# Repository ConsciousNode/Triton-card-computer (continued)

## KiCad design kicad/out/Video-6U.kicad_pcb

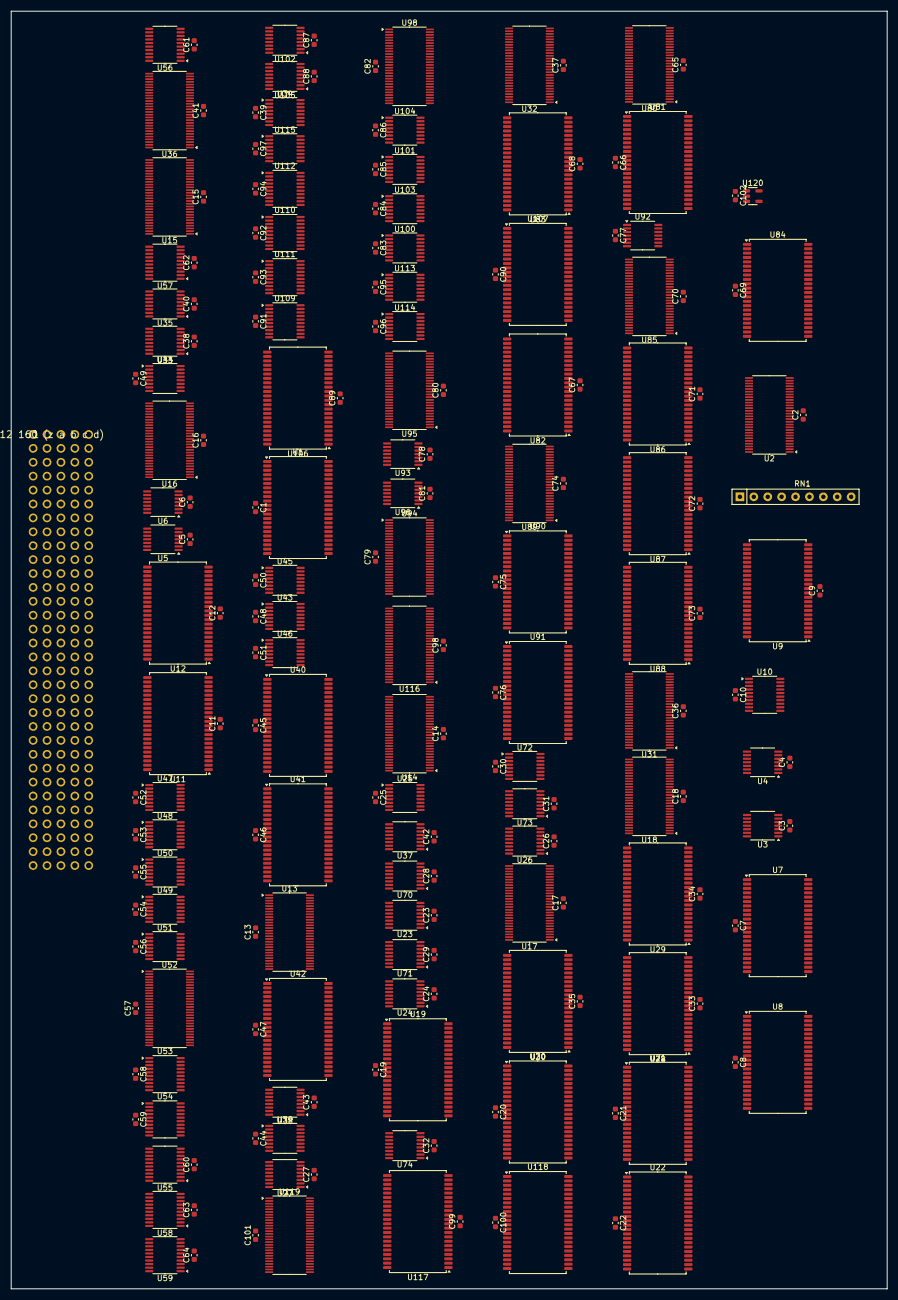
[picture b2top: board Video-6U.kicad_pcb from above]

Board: 4 copper layers, 160.0 x 233.3 mm, 206 parts (0 on the bottom side), 589 nets, no tracks yet.

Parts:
C1, C2, C3, C4, C5, C6, C7, C8, C9, C10, C11, C12, C13, C14, C15, C16, C17, C18, C19, C20, C21, C22, C23, C24, C25, C26, C27, C28, C29, C30, C31, C32, C33, C34, C35, C36, C37, C38, C39, C40, C41, C42, C43, C44, C45, C46, C47, C48, C49, C50, C51, C52, C53, C54, C55, C56, C57, C58, C59, C60, C61, C62, C63, C64, C65, C66, C67, C68, C69, C70, C71, C72, C73, C74, C75, C76, C77, C78, C79, C80, C81, C82, C83, C84, C85, C86, C87, C88, C89, C90, C91, C92, C93, C94, C95, C96, C97, C98, C99, C100, C101, C102: 100n; C_0603_1608Metric
J1: DIN41612 160 (z a b c d)
RN1: RPACK8; R_Array_SIP9
U1, U7, U8, U9, U19, U20, U21, U22, U40, U41, U42, U81, U82, U83, U84, U86, U87, U88, U90, U91, U117, U118: IS61WV5128; TSOP-II-44_10.16x18.41mm_P0.8mm
U2, U13, U14, U15, U16, U17, U18, U31, U32, U36, U52, U80, U85, U89, U94, U95, U98, U116, U119: ALVCH16823; TSSOP-56_6.1x14mm_P0.5mm
U3, U93: LVC04; TSSOP-14_4.4x5mm_P0.65mm
U4: LVC32; TSSOP-14_4.4x5mm_P0.65mm
U5, U6, U92, U96: LVC08; TSSOP-14_4.4x5mm_P0.65mm
U10: LVC574; TSSOP-20_4.4x6.5mm_P0.65mm
U11, U12, U28, U29, U30: IS61WV20488; TSOP-II-44_10.16x18.41mm_P0.8mm
U23, U24, U25, U26, U27, U33, U34, U35, U37, U38, U39, U70, U71, U72, U73, U74, U100, U101, U102, U103, U104, U105, U113, U114, U115: LVC157; TSSOP-16_4.4x5mm_P0.65mm
U43, U44, U45, U46, U47, U48, U49, U50, U51: LVC153; TSSOP-16_4.4x5mm_P0.65mm
U53, U54, U55, U56, U57, U58, U59, U109, U110, U111, U112: LVC245; TSSOP-20_4.4x6.5mm_P0.65mm
U106, U107: IS61WV51216; TSOP-II-44_10.16x18.41mm_P0.8mm
U120: LVC1G07; SOT-23-5

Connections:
+3V3: C1.1, C2.1, C3.1, C4.1, C5.1, C6.1, C7.1, C8.1, C9.1, C10.1, C11.1, C12.1, C13.1, C14.1, C15.1, C16.1, C17.1, C18.1, C19.1, C20.1, C21.1, C22.1, C23.1, C24.1, C25.1, C26.1, C27.1, C28.1, C29.1, C30.1, C31.1, C32.1, C33.1, C34.1, C35.1, C36.1, C37.1, C38.1, C39.1, C40.1, C41.1, C42.1, C43.1, C44.1, C45.1, C46.1, C47.1, C48.1, C49.1, C50.1, C51.1, C52.1, C53.1, C54.1, C55.1, C56.1, C57.1, C58.1, C59.1, C60.1, C61.1, C62.1, C63.1, C64.1, C65.1, C66.1, C67.1, C68.1, C69.1, C70.1, C71.1, C72.1, C73.1, C74.1, C75.1, C76.1, C77.1, C78.1, C79.1, C80.1, C81.1, C82.1, C83.1, C84.1, C85.1, C86.1, C87.1, C88.1, C89.1, C90.1, C91.1, C92.1, C93.1, C94.1, C95.1, C96.1, C97.1, C98.1, C99.1, C100.1, C101.1, C102.1, J1.z2, J1.z4, J1.z6, J1.z10, J1.z12, J1.z14, J1.z18, J1.z20, J1.z22, J1.z26, J1.z28, J1.z30, RN1.1, U1.11, U1.15, U1.33, U2.1, U2.7, U2.22, U2.28, U2.35, U2.50, U3.14, U4.14, U5.14, U6.14, U7.11, U7.15, U7.33, U8.11, U8.15, U8.33, U9.11, U9.15, U9.33, U10.20, U11.11, U11.15, U11.33, U12.11, U12.15, U12.33, U13.1, U13.7, U13.22, U13.28, U13.35, U13.50, U14.1, U14.7, U14.22, U14.28, U14.35, U14.50, U15.1, U15.7, U15.22, U15.28, U15.35, U15.50, U16.1, U16.7, U16.22, U16.28, U16.35, U16.50, U17.1, U17.7, U17.22, U17.28, U17.35, U17.50, U18.1, U18.7, U18.22, U18.28, U18.35, U18.50, U19.11, U19.15, U19.33, U20.11, U20.15, U20.33, U21.11, U21.15, U21.33, U22.11, U22.15, U22.33, U23.16, U24.16, U25.16, U26.16, U27.16, U28.11, U28.15, U28.33, U29.11, U29.15, U29.33, U30.11, U30.15, U30.33, U31.1, U31.7, U31.22, U31.28, U31.35, U31.50, U32.1, U32.7, U32.22, U32.28, U32.35, U32.50, U33.16, U34.16, U35.16, U36.1, U36.7, U36.22, U36.28, U36.35, U36.50, U37.16, U38.16, U39.16, U40.11, U40.15, U40.33, U41.11, U41.15, U41.33, U42.11, U42.15, U42.33, U43.16, U44.16, U45.16, U46.16, U47.16, U48.16, U49.16, U50.16, U51.16, U52.1, U52.7, U52.22, U52.28, U52.35, U52.50, U53.1, U53.20, U54.1, U54.20, U55.1, U55.20, U56.1, U56.20, U57.1, U57.20, U58.1, U58.20, U59.1, U59.20, U70.16, U71.16, U72.16, U73.16, U74.16, U80.1, U80.7, U80.22, U80.28, U80.35, U80.50, U81.11, U81.15, U81.33, U82.11, U82.15, U82.33, U83.11, U83.15, U83.33, U84.11, U84.15, U84.33, U85.1, U85.7, U85.22, U85.28, U85.35, U85.50, U86.11, U86.15, U86.33, U87.11, U87.15, U87.33, U88.11, U88.15, U88.33, U89.1, U89.7, U89.22, U89.28, U89.35, U89.50, U90.11, U90.15, U90.33, U91.11, U91.15, U91.33, U92.14, U93.14, U94.1, U94.7, U94.22, U94.28, U94.35, U94.50, U95.1, U95.7, U95.22, U95.28, U95.35, U95.50, U96.14, U98.1, U98.7, U98.22, U98.28, U98.35, U98.50, U100.16, U101.16, U102.16, U103.16, U104.16, U105.16, U106.11, U106.33, U107.11, U107.33, U109.1, U109.20, U110.1, U110.20, U111.1, U111.20, U112.1, U112.20, U113.16, U114.16, U115.16, U116.1, U116.7, U116.22, U116.28, U116.35, U116.50, U117.11, U117.15, U117.33, U118.11, U118.15, U118.33, U119.1, U119.7, U119.22, U119.28, U119.35, U119.50, U120.5
+5V: J1.z8, J1.z16, J1.z24, J1.z32
/ADB: U93.10, U107.41
/BOE: U4.3, U53.19, U54.19, U55.19, U56.19, U57.19, U58.19, U59.19
/CEDGE: J1.c13, U7.19, U8.19
/F2B: U93.4, U96.2
/FACTV: U92.13, U93.2
/FCE: U3.8, U17.30, U17.55, U18.30, U18.55
/IOCE: U5.3, U52.30, U52.55
/LDC: U7.14, U16.30, U16.55
/LDIO: U5.1, U7.36
/LDP: U7.13, U15.30, U15.55
/LDX: U7.9, U13.30, U13.55
/LDY: U7.10, U14.55
/R2: U3.4, U5.2
/SWRD: U9.14, U10.5
/SWRQ: U4.4, U10.16
/VSEL: U3.6, U4.2
/VSLD: U8.14, U14.30
/WEA: U93.6, U106.17, U109.19, U110.19
/WEB: U93.8, U107.17, U111.19, U112.19
ADB: U93.11, U98.16, U100.1, U101.1, U102.1, U103.1, U104.1, U105.1, U106.41, U113.1, U114.1, U115.1
AHS: U98.19, U116.37
APIC: U98.17, U116.38
AVS: U98.20, U116.36
AX0: U98.3, U100.2, U103.3
AX1: U98.5, U100.5, U103.6
AX2: U98.6, U100.11, U103.10
AX3: U98.8, U100.14, U103.13
AX4: U98.9, U101.2, U104.3
AX5: U98.10, U101.5, U104.6
AX6: U98.12, U101.11, U104.10
AX7: U98.13, U101.14, U104.13
AX8: U98.14, U102.2, U105.3
AX9: U98.15, U102.5, U105.6
BHS: U116.20, U119.38
BP0: U116.3, U117.3, U118.3
BP1: U116.5, U117.4, U118.4
BP2: U116.6, U117.5, U118.5
BP3: U116.8, U117.6, U118.6
BP4: U116.9, U117.7, U118.7
BP5: U116.10, U117.16, U118.16
BP6: U116.12, U117.17, U118.17
BP7: U116.13, U117.18, U118.18
BP8: U116.14, U117.19, U118.19
BP9: U116.15, U117.20, U118.20
BP10: U116.16, U117.26, U118.26
BP11: U116.17, U117.27, U118.27
BPIC: U116.19, U117.29, U118.29
BVS: U116.21, U119.37
CI0: U11.9, U13.54, U14.54
CI1: U11.10, U13.52, U14.52
CI2: U11.13, U13.51, U14.51
CI3: U11.14, U13.49, U14.49
CI4: U11.31, U13.48, U14.48
CI5: U11.32, U13.47, U14.47
CI6: U11.35, U13.45, U14.45
CI7: U11.36, U13.44, U14.44
CI8: U12.9, U13.43, U14.43
CI9: U12.10, U13.42
CLK: J1.c10, U2.29, U2.56
CNTADV: U4.9, U9.32
CNTRST: U4.10, U9.35, U19.27, U20.27, U21.27, U22.27
CO0: U23.4, U70.2
CO1: U23.7, U70.5
CO2: U23.9, U70.11
CO3: U23.12, U70.14
CO4: U24.4, U71.2
CO5: U24.7, U71.5
CO6: U24.9, U71.11
CO7: U24.12, U71.14
CO8: U25.4, U72.2
CO9: U25.7, U72.5
CO10: U25.9, U72.11
CO11: U25.12, U72.14
CO12: U26.4, U73.2
CO13: U26.7, U73.5
CO14: U26.9, U73.11
CO15: U26.12, U73.14
CO16: U27.4, U74.2
CO17: U27.7, U74.5
CO18: U27.9, U74.11
CQ0: U28.3, U29.3, U30.3, U70.4
CQ1: U28.4, U29.4, U30.4, U70.7
CQ2: U28.5, U29.5, U30.5, U70.9
CQ3: U28.6, U29.6, U30.6, U70.12
CQ4: U28.7, U29.7, U30.7, U71.4
CQ5: U28.16, U29.16, U30.16, U71.7
CQ6: U28.17, U29.17, U30.17, U71.9
CQ7: U28.18, U29.18, U30.18, U71.12
CQ8: U28.19, U29.19, U30.19, U72.4
CQ9: U28.20, U29.20, U30.20, U72.7
CQ10: U28.26, U29.26, U30.26, U72.9
CQ11: U28.27, U29.27, U30.27, U72.12
CQ12: U28.28, U29.28, U30.28, U73.4
CQ13: U28.29, U29.29, U30.29, U73.7
CQ14: U28.30, U29.30, U30.30, U73.9
CQ15: U28.38, U29.38, U30.38, U73.12
CQ16: U28.39, U29.39, U30.39, U74.4
CQ17: U28.40, U29.40, U30.40, U74.7
CQ18: U28.41, U29.41, U30.41, U74.9
CSD0: U1.9, U2.54
CSD1: U1.10, U2.52
CSD2: U1.13, U2.51
CT0: U40.9, U43.6
CT1: U40.10, U43.10
CT2: U40.13, U44.6
CT3: U40.14, U44.10
CT4: U40.31, U45.6
CT5: U40.32, U45.10
CT6: U40.35, U46.6
CT7: U40.36, U46.10
CT8: U41.9, U47.6
CT9: U41.10, U47.10
CT10: U41.13, U48.6
CT11: U41.14, U48.10
CT12: U41.31, U49.6
CT13: U41.32, U49.10
CT14: U41.35, U50.6
CT15: U41.36, U50.10
CT16: U42.9, U51.6
CT17: U42.10, U51.10
CW_/BIO: RN1.4, U2.6, U4.1
CW_/IN: RN1.2, U2.3, U7.17, U8.18
CW_/OUT: RN1.3, U2.5, U7.18
CX0: U37.4, U40.3, U41.3, U42.3
CX1: U37.7, U40.4, U41.4, U42.4
CX2: U37.9, U40.5, U41.5, U42.5
CX3: U37.12, U40.6, U41.6, U42.6
CX4: U38.4, U40.7, U41.7, U42.7
CX5: U38.7, U40.16, U41.16, U42.16
CX6: U38.9, U40.17, U41.17, U42.17
CX7: U38.12, U40.18, U41.18, U42.18
CX8: U39.4, U40.19, U41.19, U42.19
CX9: U39.7, U40.20, U41.20, U42.20
D0+: J1.a1, U11.3, U12.3, U15.54, U16.54, U53.18
D0-: J1.a2, U11.4, U12.4, U15.52, U16.52, U53.17
D1+: J1.a3, U11.5, U12.5, U15.51, U16.51, U53.16
D1-: J1.a4, U11.6, U12.6, U15.49, U16.49, U53.15
D2+: J1.a5, U11.7, U12.7, U15.48, U16.48, U53.14
D2-: J1.a6, U11.16, U12.16, U15.47, U16.47, U53.13
D3+: J1.a7, U5.4, U11.17, U12.17, U53.12
D3-: J1.a9, U5.9, U11.18, U12.18, U53.11
D4+: J1.a10, U5.12, U11.19, U12.19, U54.18
D4-: J1.a11, U6.1, U11.20, U12.20, U54.17
D5+: J1.a12, U6.4, U11.26, U12.26, U54.16
D5-: J1.a13, U6.9, U11.27, U12.27, U54.15
D6+: J1.a14, U11.28, U12.28, U54.14
D6-: J1.a15, U11.29, U12.29, U54.13
D7+: J1.a17, U11.30, U12.30, U54.12
D7-: J1.a18, U11.38, U12.38, U54.11
D8+: J1.a19, U11.39, U12.39, U55.18
D8-: J1.a20, U11.40, U12.40, U55.17
D9+: J1.a21, U55.16
D9-: J1.a22, U55.15
D10+: J1.a23, U55.14
D10-: J1.a25, U55.13
D11+: J1.a26, U55.12
D11-: J1.a27, U55.11
D12+: J1.a28, U56.18
D12-: J1.a29, U56.17
D13+: J1.a30, U56.16
D13-: J1.a31, U56.15
D14+: J1.b1, U56.14
D14-: J1.b2, U56.13
D15+: J1.b3, U56.12
D15-: J1.b4, U56.11
D16+: J1.b5, U57.18
D16-: J1.b6, U57.17
D17+: J1.b7, U57.16
D17-: J1.b9, U57.15
D18+: J1.b10, U57.14
D18-: J1.b11, U57.13
D19+: J1.b12, U57.12
D19-: J1.b13, U57.11
D20+: J1.b14, U58.18
D20-: J1.b15, U58.17
D21+: J1.b17, U58.16
D21-: J1.b18, U58.15
D22+: J1.b19, U58.14
D22-: J1.b20, U58.13
D23+: J1.b21, U58.12
D23-: J1.b22, U58.11
D24+: J1.b23, U59.18
D24-: J1.b25, U59.17
D25+: J1.b26, U59.16
D25-: J1.b27, U59.15
D26+: J1.b28, U59.14
D26-: J1.b29, U59.13
DB: U87.32, U98.41
F1B: U94.16, U95.41
F1V: U94.17, U95.40
F1X0: U94.3, U95.54
F1X1: U94.5, U95.52
F1X2: U94.6, U95.51
F1X3: U94.8, U95.49
F1X4: U94.9, U95.48
F1X5: U94.10, U95.47
F1X6: U94.12, U95.45
F1X7: U94.13, U95.44
F1X8: U94.14, U95.43
F1X9: U94.15, U95.42
F2B: U93.3, U95.16, U96.5
F2V: U95.17, U96.1, U96.4
F2X0: U95.3, U100.3, U103.2
F2X1: U95.5, U100.6, U103.5
F2X2: U95.6, U100.10, U103.11
F2X3: U95.8, U100.13, U103.14
F2X4: U95.9, U101.3, U104.2
F2X5: U95.10, U101.6, U104.5
F2X6: U95.12, U101.10, U104.11
F2X7: U95.13, U101.13, U104.14
F2X8: U95.14, U102.3, U105.2
F2X9: U95.15, U102.6, U105.5
FACT: U89.16, U92.1
FACT2: U92.3, U92.4
FACTV: U92.6, U92.9, U93.1
FB: U87.35, U94.41
FC0: U16.3, U33.3, U43.5
FC1: U16.5, U33.6, U43.11
FC2: U16.6, U33.10, U44.5
FC3: U16.8, U33.13, U44.11
FC4: U16.9, U34.3, U45.5
FC5: U16.10, U34.6, U45.11
FC6: U16.12, U34.10, U46.5
FC7: U16.13, U34.13, U46.11
FC8: U16.14, U35.3, U47.5
FC9: U16.15, U35.6, U47.11
FC10: U16.16, U35.10, U48.5
FC11: U16.17, U35.13, U48.11
FCNT: U3.9, U4.8
FDONE: U9.17, U22.10
FFXN0: U89.54, U90.9
FFXN1: U89.52, U90.10
FFXN2: U89.51, U90.13
FFXN3: U89.49, U90.14
FFXN4: U89.48, U90.31
FFXN5: U89.47, U90.32
FFXN6: U89.45, U90.35
FFXN7: U89.44, U90.36
FFXN8: U89.43, U91.9
FFXN9: U89.42, U91.10
FL: U9.16, U10.17, U23.1, U24.1, U25.1, U26.1, U27.1, U33.1, U34.1, U35.1
FLINE: U87.31, U92.2
FNOW: U28.42, U29.42, U30.42, U70.1, U71.1, U72.1, U73.1, U74.1, U90.27, U91.27, U92.8, U94.40
FREE: U3.2, U92.10, U92.12
FREEOP: U9.18, U92.11
FWIN: U84.9, U92.5
FX0: U17.3, U19.3, U20.3, U23.3
FX1: U17.5, U19.4, U20.4, U23.6
FX2: U17.6, U19.5, U20.5, U23.10
FX3: U17.8, U19.6, U20.6, U23.13
FX4: U17.9, U19.7, U20.7, U24.3
FX5: U17.10, U19.16, U20.16, U24.6
FX6: U17.12, U19.17, U20.17, U24.10
FX7: U17.13, U19.18, U20.18, U24.13
FX8: U17.14, U19.19, U20.19, U25.3
FX9: U17.15, U19.20, U20.20, U25.6
FXC0: U70.3, U89.3, U90.3, U91.3, U94.54
FXC1: U70.6, U89.5, U90.4, U91.4, U94.52
FXC2: U70.10, U89.6, U90.5, U91.5, U94.51
FXC3: U70.13, U89.8, U90.6, U91.6, U94.49
FXC4: U71.3, U89.9, U90.7, U91.7, U94.48
FXC5: U71.6, U89.10, U90.16, U91.16, U94.47
FXC6: U71.10, U89.12, U90.17, U91.17, U94.45
FXC7: U71.13, U89.13, U90.18, U91.18, U94.44
FXC8: U72.3, U89.14, U90.19, U91.19, U94.43
FXC9: U72.6, U89.15, U90.20, U91.20, U94.42
FXN0: U17.54, U19.9
FXN1: U17.52, U19.10
FXN2: U17.51, U19.13
FXN3: U17.49, U19.14
FXN4: U17.48, U19.31
FXN5: U17.47, U19.32
FXN6: U17.45, U19.35
FXN7: U17.44, U19.36
FXN8: U17.43, U20.9
FXN9: U17.42, U20.10
FY0: U18.3, U21.3, U22.3, U25.10
FY1: U18.5, U21.4, U22.4, U25.13
FY2: U18.6, U21.5, U22.5, U26.3
FY3: U18.8, U21.6, U22.6, U26.6
FY4: U18.9, U21.7, U22.7, U26.10
FY5: U18.10, U21.16, U22.16, U26.13
FY6: U18.12, U21.17, U22.17, U27.3
FY7: U18.13, U21.18, U22.18, U27.6
FY8: U18.14, U21.19, U22.19, U27.10
FYN0: U18.54, U21.9
FYN1: U18.52, U21.10
FYN2: U18.51, U21.13
FYN3: U18.49, U21.14
FYN4: U18.48, U21.31
FYN5: U18.47, U21.32
FYN6: U18.45, U21.35
FYN7: U18.44, U21.36
FYN8: U18.43, U22.9
GND: C1.2, C2.2, C3.2, C4.2, C5.2, C6.2, C7.2, C8.2, C9.2, C10.2, C11.2, C12.2, C13.2, C14.2, C15.2, C16.2, C17.2, C18.2, C19.2, C20.2, C21.2, C22.2, C23.2, C24.2, C25.2, C26.2, C27.2, C28.2, C29.2, C30.2, C31.2, C32.2, C33.2, C34.2, C35.2, C36.2, C37.2, C38.2, C39.2, C40.2, C41.2, C42.2, C43.2, C44.2, C45.2, C46.2, C47.2, C48.2, C49.2, C50.2, C51.2, C52.2, C53.2, C54.2, C55.2, C56.2, C57.2, C58.2, C59.2, C60.2, C61.2, C62.2, C63.2, C64.2, C65.2, C66.2, C67.2, C68.2, C69.2, C70.2, C71.2, C72.2, C73.2, C74.2, C75.2, C76.2, C77.2, C78.2, C79.2, C80.2, C81.2, C82.2, C83.2, C84.2, C85.2, C86.2, C87.2, C88.2, C89.2, C90.2, C91.2, C92.2, C93.2, C94.2, C95.2, C96.2, C97.2, C98.2, C99.2, C100.2, C101.2, C102.2, J1.a8, J1.a16, J1.a24, J1.a32, J1.b8, J1.b16, J1.b24, J1.b32, J1.c8, J1.c16, J1.c24, J1.c32, J1.d8, J1.d16, J1.d24, J1.d32, J1.z1, J1.z3, J1.z5, J1.z7, J1.z9, J1.z11, J1.z13, J1.z15, J1.z17, J1.z19, J1.z21, J1.z23, J1.z25, J1.z27, J1.z29, J1.z31, U1.8, U1.12, U1.26, U1.27, U1.28, U1.29, U1.30, U1.34, U1.37, U1.38, U1.39, U1.40, U1.41, U2.4, U2.11, U2.18, U2.25, U2.30, U2.31, U2.32, U2.33, U2.34, U2.36, U2.37, U2.38, U2.39, U2.40, U2.41, U2.42, U2.43, U2.44, U2.45, U2.46, U2.47, U2.48, U2.49, U2.53, U2.55, U3.7, U4.7, U4.12, U4.13, U5.7, U6.7, U6.12, U6.13, U7.8, U7.12, U7.20, U7.26, U7.27, U7.28, U7.29, U7.30, U7.34, U7.37, U7.38, U7.39, U7.40, U7.41, U8.8, U8.12, U8.20, U8.26, U8.27, U8.28, U8.29, U8.30, U8.34, U8.37, U8.38, U8.39, U8.40, U8.41, U9.8, U9.12, U9.27, U9.28, U9.29, U9.30, U9.34, U9.37, U9.38, U9.39, U9.40, U9.41, U10.1, U10.8, U10.9, U10.10, U11.8, U11.12, U11.34, U11.37, U11.42, U12.8, U12.12, U12.34, U12.37, U12.42, U13.2, U13.4, U13.11, U13.18, U13.25, U13.27, U13.31, U13.32, U13.33, U13.34, U13.36, U13.37, U13.38, U13.39, U13.40, U13.41, U13.46, U13.53, U14.2, U14.4, U14.11, U14.18, U14.25, U14.27, U14.31, U14.32, U14.33, U14.34, U14.36, U14.37, U14.38, U14.39, U14.40, U14.41, U14.46, U14.53, U15.2, U15.4, U15.11, U15.18, U15.25, U15.27, U15.31, U15.32, U15.33, U15.34, U15.36, U15.37, U15.38, U15.39, U15.46, U15.53, U16.2, U16.4, U16.11, U16.18, U16.25, U16.27, U16.31, U16.32, U16.33, U16.34, U16.36, U16.37, U16.38, U16.39, U16.46, U16.53, U17.2, U17.4, U17.11, U17.18, U17.25, U17.27, U17.31, U17.32, U17.33, U17.34, U17.36, U17.37, U17.38, U17.39, U17.40, U17.41, U17.46, U17.53, U18.2, U18.4, U18.11, U18.18, U18.25, U18.27, U18.31, U18.32, U18.33, U18.34, U18.36, U18.37, U18.38, U18.39, U18.40, U18.41, U18.42, U18.46, U18.53, U19.8, U19.12, U19.28, U19.29, U19.30, U19.34, U19.37, U19.38, U19.39, U19.40, U19.41, U20.8, U20.12, U20.28, U20.29, U20.30, U20.34, U20.37, U20.38, U20.39, U20.40, U20.41, U21.8, U21.12, U21.28, U21.29, U21.30, U21.34, U21.37, U21.38, U21.39, U21.40, U21.41, U22.8, U22.12, U22.28, U22.29, U22.30, U22.34, U22.37, U22.38, U22.39, U22.40, U22.41, U23.8, U23.15, U24.8, U24.15, U25.8, U25.15, U26.8, U26.15, U27.8, U27.13, U27.14, U27.15, U28.8, U28.12, U28.34, U28.37, U29.8, U29.12, U29.34, U29.37, U30.8, U30.12, U30.34, U30.37, U31.2, U31.4, U31.11, U31.18, U31.25, U31.27, U31.30, U31.32, U31.39, U31.46, U31.53, U31.55, U32.2, U32.4, U32.11, U32.18, U32.25, U32.27, U32.30, U32.31, U32.32, U32.33, U32.34, U32.36, U32.37, U32.38, U32.39, U32.40, U32.41, U32.42, U32.43, U32.44, U32.45, U32.46, U32.47, U32.48, U32.49, U32.51, U32.52, U32.53, U32.55, U33.8, U33.15, U34.8, U34.15, U35.8, U35.15, U36.2, U36.4, U36.11, U36.18, U36.25, U36.27, U36.30, U36.31, U36.32, U36.33, U36.34, U36.36, U36.37, U36.38, U36.39, U36.46, U36.53, U36.55, U37.8, U37.15, U38.8, U38.15, U39.6, U39.8, U39.10, U39.11, U39.13, U39.14, U39.15, U40.8, U40.12, U40.26, U40.27, U40.28, U40.29, U40.30, U40.34, U40.37, U40.38, U40.39, U40.40, U40.41, U41.8, U41.12, U41.26, U41.27, U41.28, U41.29, U41.30, U41.34, U41.37, U41.38, U41.39, U41.40, U41.41, U42.8, U42.12, U42.26, U42.27, U42.28, U42.29, U42.30, U42.34, U42.37, U42.38, U42.39, U42.40, U42.41, U43.1, U43.3, U43.8, U43.13, U43.15, U44.1, U44.3, U44.8, U44.13, U44.15, U45.1, U45.3, U45.8, U45.13, U45.15, U46.1, U46.3, U46.8, U46.13, U46.15, U47.1, U47.3, U47.8, U47.13, U47.15, U48.1, U48.3, U48.8, U48.13, U48.15, U49.1, U49.3, U49.4, U49.5, U49.8, U49.11, U49.12, U49.13, U49.15, U50.1, U50.3, U50.4, U50.5, U50.8, U50.11, U50.12, U50.13, U50.15, U51.1, U51.3, U51.4, U51.5, U51.8, U51.11, U51.12, U51.13, U51.15, U52.2, U52.4, U52.11, U52.18, U52.25, U52.27, U52.32, U52.39, U52.46, U52.53, U53.10, U54.10, U55.4, U55.5, U55.6, U55.7, U55.8, U55.9, U55.10, U56.2, U56.3, U56.4, U56.5, U56.6, U56.7, U56.8, U56.9, U56.10, U57.2, U57.3, U57.4, U57.5, U57.6, U57.7, U57.8, U57.9, U57.10, U58.2, U58.3, U58.4, U58.5, U58.6, U58.7, U58.8, U58.9, U58.10, U59.2, U59.3, U59.4, U59.5, U59.6, U59.7, U59.8, U59.9, U59.10, U70.8, U70.15, U71.8, U71.15, U72.8, U72.15, U73.8, U73.15, U74.8, U74.13, U74.14, U74.15, U80.2, U80.4, U80.11, U80.18, U80.25, U80.27, U80.30, U80.31, U80.32, U80.33, U80.34, U80.36, U80.37, U80.38, U80.39, U80.40, U80.46, U80.53, U80.55, U81.8, U81.12, U81.27, U81.28, U81.29, U81.30, U81.34, U81.37, U81.38, U81.39, U81.40, U81.41, U82.8, U82.12, U82.27, U82.28, U82.29, U82.30, U82.34, U82.37, U82.38, U82.39, U82.40, U82.41, U83.8, U83.12, U83.27, U83.28, U83.29, U83.30, U83.34, U83.37, U83.38, U83.39, U83.40, U83.41, U84.8, U84.12, U84.27, U84.28, U84.29, U84.30, U84.34, U84.37, U84.38, U84.39, U84.40, U84.41, U85.2, U85.4, U85.11, U85.18, U85.25, U85.27, U85.30, U85.31, U85.32, U85.33, U85.34, U85.36, U85.37, U85.38, U85.39, U85.40, U85.41, U85.46, U85.53, U85.55, U86.8, U86.12, U86.27, U86.28, U86.29, U86.30, U86.34, U86.37, U86.38, U86.39, U86.40, U86.41, U87.8, U87.12, U87.27, U87.28, U87.29, U87.30, U87.34, U87.37, U87.38, U87.39, U87.40, U87.41, U88.8, U88.12, U88.27, U88.28, U88.29, U88.30, U88.34, U88.37, U88.38, U88.39, U88.40, U88.41, U89.2, U89.4, U89.11, U89.18, U89.25, U89.27, U89.30, U89.31, U89.32, U89.33, U89.34, U89.36, U89.37, U89.38, U89.39, U89.40, U89.46, U89.53, U89.55, U90.8, U90.12, U90.28, U90.29, U90.30, U90.34, U90.37, U90.38, U90.39, U90.40, U90.41, U91.8, U91.12, U91.28, U91.29, U91.30, U91.34, U91.37, U91.38, U91.39, U91.40, U91.41, U92.7, U93.7, U94.2, U94.4, U94.11, U94.18, U94.25, U94.27, U94.30, U94.31, U94.32, U94.33, U94.34, U94.36, U94.37, U94.38, U94.39, U94.46, U94.53, U94.55, U95.2, U95.4, U95.11, U95.18, U95.25, U95.27, U95.30, U95.31, U95.32, U95.33, U95.34, U95.36, U95.37, U95.38, U95.39, U95.46, U95.53, U95.55, U96.7, U96.12, U96.13, U98.2, U98.4, U98.11, U98.18, U98.25, U98.27, U98.30, U98.31, U98.32, U98.33, U98.34, U98.36, U98.39, U98.46, U98.53, U98.55, U100.8, U100.15, U101.8, U101.15, U102.8, U102.10, U102.11, U102.13, U102.14, U102.15, U103.8, U103.15, U104.8, U104.15, U105.8, U105.10, U105.11, U105.13, U105.14, U105.15, U106.6, U106.12, U106.23, U106.24, U106.25, U106.26, U106.27, U106.28, U106.34, U106.39, U106.40, U106.42, U106.43, U106.44, U107.6, U107.12, U107.23, U107.24, U107.25, U107.26, U107.27, U107.28, U107.34, U107.39, U107.40, U107.42, U107.43, U107.44, U109.10, U110.6, U110.7, U110.8, U110.9, U110.10, U111.10, U112.6, U112.7, U112.8, U112.9, U112.10, U113.8, U113.15, U114.8, U114.15, U115.8, U115.15, U116.2, U116.4, U116.11, U116.18, U116.25, U116.27, U116.30, U116.31, U116.32, U116.33, U116.34, U116.39, U116.46, U116.53, U116.55, U117.8, U117.12, U117.30, U117.34, U117.37, U117.38, U117.39, U117.40, U117.41, U118.8, U118.12, U118.30, U118.34, U118.37, U118.38, U118.39, U118.40, U118.41, U119.2, U119.4, U119.11, U119.18, U119.25, U119.27, U119.30, U119.31, U119.32, U119.33, U119.34, U119.36, U119.39, U119.46, U119.53, U119.55, U120.3
HC0: U80.3, U81.3, U82.3, U83.3, U84.3
HC1: U80.5, U81.4, U82.4, U83.4, U84.4
HC2: U80.6, U81.5, U82.5, U83.5, U84.5
HC3: U80.8, U81.6, U82.6, U83.6, U84.6
HC4: U80.9, U81.7, U82.7, U83.7, U84.7
HC5: U80.10, U81.16, U82.16, U83.16, U84.16
HC6: U80.12, U81.17, U82.17, U83.17, U84.17
HC7: U80.13, U81.18, U82.18, U83.18, U84.18
HC8: U80.14, U81.19, U82.19, U83.19, U84.19
HC9: U80.15, U81.20, U82.20, U83.20, U84.20
HC10: U80.16, U81.26, U82.26, U83.26, U84.26
HN0: U80.54, U81.9
HN1: U80.52, U81.10
HN2: U80.51, U81.13
HN3: U80.49, U81.14
HN4: U80.48, U81.31
HN5: U80.47, U81.32
HN6: U80.45, U81.35
HN7: U80.44, U81.36
HN8: U80.43, U82.9
HN9: U80.42, U82.10
HN10: U80.41, U82.13
HPIC: U82.31, U96.9
HS: U82.14, U98.38
IOD0: U52.3, U53.2
IOD1: U52.5, U53.3
IOD2: U52.6, U53.4
IOD3: U52.8, U53.5
IOD4: U52.9, U53.6
IOD5: U52.10, U53.7
IOD6: U52.12, U53.8
IOD7: U52.13, U53.9
IOD8: U52.14, U54.2
IOD9: U52.15, U54.3
IOD10: U52.16, U54.4
IOD11: U52.17, U54.5
IOD12: U52.19, U54.6
IOD13: U52.20, U54.7
IOD14: U52.21, U54.8
IOD15: U52.23, U54.9
IOD16: U52.24, U55.2
IOD17: U52.26, U55.3
ION0: U43.7, U52.54
ION1: U43.9, U52.52
ION2: U44.7, U52.51
ION3: U44.9, U52.49
ION4: U45.7, U52.48
ION5: U45.9, U52.47
ION6: U46.7, U52.45
ION7: U46.9, U52.44
ION8: U47.7, U52.43
ION9: U47.9, U52.42
ION10: U48.7, U52.41
ION11: U48.9, U52.40
ION12: U49.7, U52.38
ION13: U49.9, U52.37
ION14: U50.7, U52.36
ION15: U50.9, U52.34
ION16: U51.7, U52.33
ION17: U51.9, U52.31
IORDY: J1.d4, U120.4
LA0: U106.7, U109.18, U113.2
LA1: U106.8, U109.17, U113.5
LA2: U106.9, U109.16, U113.11
LA3: U106.10, U109.15, U113.14
LA4: U106.13, U109.14, U114.2
LA5: U106.14, U109.13, U114.5
LA6: U106.15, U109.12, U114.11
LA7: U106.16, U109.11, U114.14
LA8: U106.29, U110.18, U115.2
LA9: U106.30, U110.17, U115.5
LA10: U106.31, U110.16, U115.11
LA11: U106.32, U110.15, U115.14
LAA0: U100.4, U106.1
LAA1: U100.7, U106.2
LAA2: U100.9, U106.3
LAA3: U100.12, U106.4
LAA4: U101.4, U106.5
LAA5: U101.7, U106.18
LAA6: U101.9, U106.19
LAA7: U101.12, U106.20
LAA8: U102.4, U106.21
LAA9: U102.7, U106.22
LB0: U107.7, U111.18, U113.3
LB1: U107.8, U111.17, U113.6
LB2: U107.9, U111.16, U113.10
LB3: U107.10, U111.15, U113.13
LB4: U107.13, U111.14, U114.3
LB5: U107.14, U111.13, U114.6
LB6: U107.15, U111.12, U114.10
LB7: U107.16, U111.11, U114.13
LB8: U107.29, U112.18, U115.3
LB9: U107.30, U112.17, U115.6
LB10: U107.31, U112.16, U115.10
LB11: U107.32, U112.15, U115.13
LBA0: U103.4, U107.1
LBA1: U103.7, U107.2
LBA2: U103.9, U107.3
LBA3: U103.12, U107.4
LBA4: U104.4, U107.5
LBA5: U104.7, U107.18
LBA6: U104.9, U107.19
LBA7: U104.12, U107.20
LBA8: U105.4, U107.21
LBA9: U105.7, U107.22
LEND: U82.32, U86.26, U87.26, U88.26, U90.26, U91.26
LR0: U113.4, U116.54
LR1: U113.7, U116.52
LR2: U113.9, U116.51
LR3: U113.12, U116.49
LR4: U114.4, U116.48
LR5: U114.7, U116.47
LR6: U114.9, U116.45
LR7: U114.12, U116.44
LR8: U115.4, U116.43
LR9: U115.7, U116.42
LR10: U115.9, U116.41
LR11: U115.12, U116.40
MODE: J1.d23, U5.5, U5.10, U5.13, U6.2, U6.5, U6.10, U11.41, U12.41, U19.26, U20.26, U21.20, U22.20, U28.25, U29.25, U30.25, U117.28, U118.28
NFACT: U89.41, U91.13
NFL: U9.13, U10.4
NPR: U9.10, U10.3
NPW: U9.9, U10.2
PA0: U28.9, U31.54
PA1: U28.10, U31.52
PA2: U28.13, U31.51
PA3: U28.14, U31.49
PA4: U28.31, U31.48
PA5: U28.32, U31.47
PA6: U28.35, U31.45
PA7: U28.36, U31.44
PA8: U29.9, U31.43
PA9: U29.10, U31.42
PA10: U29.13, U31.41
PA11: U29.14, U31.40
PA12: U29.31, U31.38
PA13: U29.32, U31.37
PA14: U29.35, U31.36
PA15: U29.36, U31.34
PA16: U30.9, U31.33
PA17: U30.10, U31.31
PA18: U30.13, U32.54
PD0: U117.9, U119.54
PD1: U117.10, U119.52
PD2: U117.13, U119.51
PD3: U117.14, U119.49
PD4: U117.31, U119.48
PD5: U117.32, U119.47
PD6: U117.35, U119.45
PD7: U117.36, U119.44
PD8: U118.9, U119.43
PD9: U118.10, U119.42
PD10: U118.13, U119.41
PD11: U118.14, U119.40
PIC: U96.8, U98.40
PORT0: J1.d17, U7.3, U8.3, U11.25, U12.25
PORT1: J1.d18, U7.4, U8.4
PORT2: J1.d19, U7.5, U8.5
PORT3: J1.d20, U7.6, U8.6
PORT4: J1.d21, U7.7, U8.7
PORT5: J1.d22, U7.16, U8.16
PR: U9.7, U10.18
PV6: U5.6, U15.45, U16.45
PV7: U5.8, U15.44, U16.44
PV8: U5.11, U15.43, U16.43
PV9: U6.3, U15.42, U16.42
PV10: U6.6, U15.41, U16.41
PV11: U6.8, U15.40, U16.40
PW: U9.6, U10.19
PX0: U15.3, U33.2
PX1: U15.5, U33.5
PX2: U15.6, U33.11
PX3: U15.8, U33.14
PX4: U15.9, U34.2
PX5: U15.10, U34.5
PX6: U15.12, U34.11
PX7: U15.13, U34.14
PX8: U15.14, U35.2
PX9: U15.15, U35.5
PX10: U15.16, U35.11
PX11: U15.17, U35.14
PY0: U72.10, U88.9
PY1: U72.13, U88.10
PY2: U73.3, U88.13
PY3: U73.6, U88.14
PY4: U73.10, U88.31
PY5: U73.13, U88.32
PY6: U74.3, U88.35
PY7: U74.6, U88.36
PY8: U74.10, U87.36
R1: U9.19, U10.7, U10.15
R1D: U9.31, U10.6
R2: U3.3, U8.17, U9.20, U10.14
READY: U9.36, U120.2
RESET: J1.c12, U2.2, U2.27, U4.5, U9.26
SCLK: J1.c11, U10.11, U13.29, U13.56, U14.29, U14.56, U15.29, U15.56, U16.29, U16.56, U17.29, U17.56, U18.29, U18.56, U31.29, U31.56, U32.29, U32.56, U36.29, U36.56, U52.29, U52.56, U80.29, U80.56, U85.29, U85.56, U89.29, U89.56, U94.29, U94.56, U95.29, U95.56, U98.29, U98.56, U116.29, U116.56, U119.29, U119.56
SEL0: U8.9, U43.14, U44.14, U45.14, U46.14, U47.14, U48.14, U49.14, U50.14, U51.14
SEL1: U8.10, U43.2, U44.2, U45.2, U46.2, U47.2, U48.2, U49.2, U50.2, U51.2
SETFL: U7.32, U9.4
SETPR: U7.35, U9.5
SETPW: U7.31, U9.3
SIN0: U33.4, U36.54
SIN1: U33.7, U36.52
SIN2: U33.9, U36.51
SIN3: U33.12, U36.49
SIN4: U34.4, U36.48
SIN5: U34.7, U36.47
SIN6: U34.9, U36.45
SIN7: U34.12, U36.44
SIN8: U35.4, U36.43
SIN9: U35.7, U36.42
SIN10: U35.9, U36.41
SIN11: U35.12, U36.40
SO0: U43.4, U109.2, U111.2
SO1: U43.12, U109.3, U111.3
SO2: U44.4, U109.4, U111.4
SO3: U44.12, U109.5, U111.5
SO4: U45.4, U109.6, U111.6
SO5: U45.12, U109.7, U111.7
SO6: U46.4, U109.8, U111.8
SO7: U46.12, U109.9, U111.9
SO8: U47.4, U110.2, U112.2
SO9: U47.12, U110.3, U112.3
SO10: U48.4, U110.4, U112.4
SO11: U48.12, U110.5, U112.5
UA0: J1.b30, U1.3
UA1: J1.b31, U1.4
UA2: J1.c1, U1.5
UA3: J1.c2, U1.6
UA4: J1.c3, U1.7
UA5: J1.c4, U1.16
UA6: J1.c5, U1.17
UA7: J1.c6, U1.18
UA8: J1.c7, U1.19
UA9: J1.c9, U1.20
VC0: U85.3, U86.3, U87.3, U88.3
VC1: U85.5, U86.4, U87.4, U88.4
VC2: U85.6, U86.5, U87.5, U88.5
VC3: U85.8, U86.6, U87.6, U88.6
VC4: U85.9, U86.7, U87.7, U88.7
VC5: U85.10, U86.16, U87.16, U88.16
VC6: U85.12, U86.17, U87.17, U88.17
VC7: U85.13, U86.18, U87.18, U88.18
VC8: U85.14, U86.19, U87.19, U88.19
VC9: U85.15, U86.20, U87.20, U88.20
VN0: U85.54, U86.9
VN1: U85.52, U86.10
VN2: U85.51, U86.13
VN3: U85.49, U86.14
VN4: U85.48, U86.31
VN5: U85.47, U86.32
VN6: U85.45, U86.35
VN7: U85.44, U86.36
VN8: U85.43, U87.9
VN9: U85.42, U87.10
VPIC: U87.14, U96.10
VS: U87.13, U98.37
VSEL: U3.5, U14.15
VSELD: U8.13, U14.42
WEA: U93.5, U96.3
WEB: U93.9, U96.6
WRAPX: U20.13, U21.26, U22.26
X0: U13.3, U23.2, U37.2
X1: U13.5, U23.5, U37.5
X2: U13.6, U23.11, U37.11
X3: U13.8, U23.14, U37.14
X4: U13.9, U24.2, U38.2
X5: U13.10, U24.5, U38.5
X6: U13.12, U24.11, U38.11
X7: U13.13, U24.14, U38.14
X8: U13.14, U25.2, U39.2
X9: U13.15, U25.5, U39.5
XD0: U83.9, U98.54
XD1: U83.10, U98.52
XD2: U83.13, U98.51
XD3: U83.14, U98.49
XD4: U83.31, U98.48
XD5: U83.32, U98.47
XD6: U83.35, U98.45
XD7: U83.36, U98.44
XD8: U82.35, U98.43
XD9: U82.36, U98.42
Y0: U14.3, U25.11, U37.3
Y1: U14.5, U25.14, U37.6
Y2: U14.6, U26.2, U37.10
Y3: U14.8, U26.5, U37.13
Y4: U14.9, U26.11, U38.3
Y5: U14.10, U26.14, U38.6
Y6: U14.12, U27.2, U38.10
Y7: U14.13, U27.5, U38.13
Y8: U14.14, U27.11, U39.3
YSEL: U8.31, U37.1, U38.1, U39.1
